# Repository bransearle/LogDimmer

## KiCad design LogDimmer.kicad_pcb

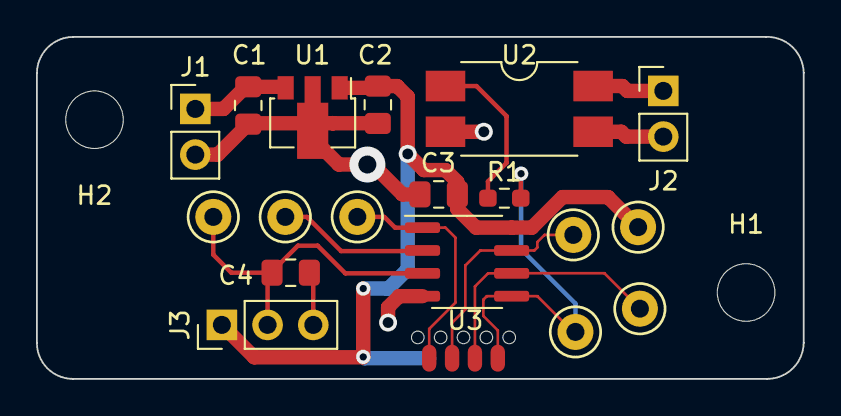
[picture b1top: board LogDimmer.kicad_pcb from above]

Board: 2 copper layers, 42.6 x 19.0 mm, 21 parts (1 on the bottom side), 12 nets.

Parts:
C1: 330n; C_0805_2012Metric_Pad1.18x1.45mm_HandSolder
C2, C3, C4: 100n; C_0805_2012Metric_Pad1.18x1.45mm_HandSolder
DBG1: AVRISP_SOICbite; SOICbite
H1, H2: MountingHole; MountingHole_3.2mm_M3_DIN965
J1: Conn_01x02; PinHeader_1x02_P2.54mm_Vertical
J2: LED-PSU; PinHeader_1x02_P2.54mm_Vertical
J3: POT; PinHeader_1x03_P2.54mm_Vertical
R1: 68R; R_0603_1608Metric_Pad0.98x0.95mm_HandSolder
TP1: PB0; TestPoint_Keystone_5000-5004_Miniature
TP2: PB1; TestPoint_Keystone_5000-5004_Miniature
TP3: PB2; TestPoint_Keystone_5000-5004_Miniature
TP4: PB3; TestPoint_Keystone_5000-5004_Miniature
TP5: PB4; TestPoint_Keystone_5000-5004_Miniature
TP6: PB5; TestPoint_Keystone_5000-5004_Miniature
TP7: 3V3; TestPoint_Keystone_5000-5004_Miniature
U1: L78L33_SOT89; SOT-89-3
U2: PC817X3; SMD-4-Optocoupler
U3: ATtiny13A-SS; SOIC-8_3.9x4.9mm_P1.27mm

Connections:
+3V3: C2.1, C3.1, DBG1.1 (VCC), J3.1, TP7.1 (TP), U1.1 (OUT), U3.8 (VCC)
+5V: C1.2, J1.1, U1.3 (IN)
/DIM+: J2.1, U2.4
/DIM-: J2.2, U2.3
GND: C1.1, C2.2, C3.2, C4.1, DBG1.4 (GND), J1.2, J3.3, U1.2 (GND), U2.2, U3.4 (GND)
MISO: DBG1.6 (MISO), TP2.1 (TP), U3.6 (PB1)
MOSI: DBG1.5 (MOSI), R1.1, TP1.1 (TP), U3.5 (PB0)
unnamed: C4.2, J3.2, TP5.1 (TP), U3.3 (PB4)
unnamed: R1.2, U2.1
unnamed: TP4.1 (TP), U3.2 (PB3)
SCK: DBG1.7 (SCK), TP3.1 (TP), U3.7 (PB2)
~RST: DBG1.8 (~RST), TP6.1 (TP), U3.1 (~RESET/PB5)

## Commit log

2022-07-05 initial
2022-07-12 Footprints assigned, PCB import.
2022-07-12 Initial placements done. JRC design rules entered in project.
    Design rule copper-to-hole limit dialled down to 0.2mm to allow for SOICbite breakout routing.
2022-10-19 Initial routing done
2022-10-19 DRC clearing & silks
2022-10-20 trying Kibot buildchain
2022-10-20 retry
2022-10-20 updating gitignore
2022-10-20 updating upload-artifact to v3
2022-10-21 Changes to KiBot config
2022-10-21 fixing gitignore for project backup
2022-10-21 Corrected PCBWay output location
2022-10-21 maybe adding hash to output?
2022-10-21 didn't quite work, trying again
2022-10-21 again
2022-10-21 whoops, YAML syntax!
2022-10-21 now workflow issue
2022-10-21 are env vars even working?
2022-10-21 no they are not, maybe syntax?
2022-10-21 aha yes, needs expanded syntax?
2022-10-21 getting there, looks like problem with hash shortening now
2022-10-22 Removing attempts at including hash, adding mount holes to schematic
